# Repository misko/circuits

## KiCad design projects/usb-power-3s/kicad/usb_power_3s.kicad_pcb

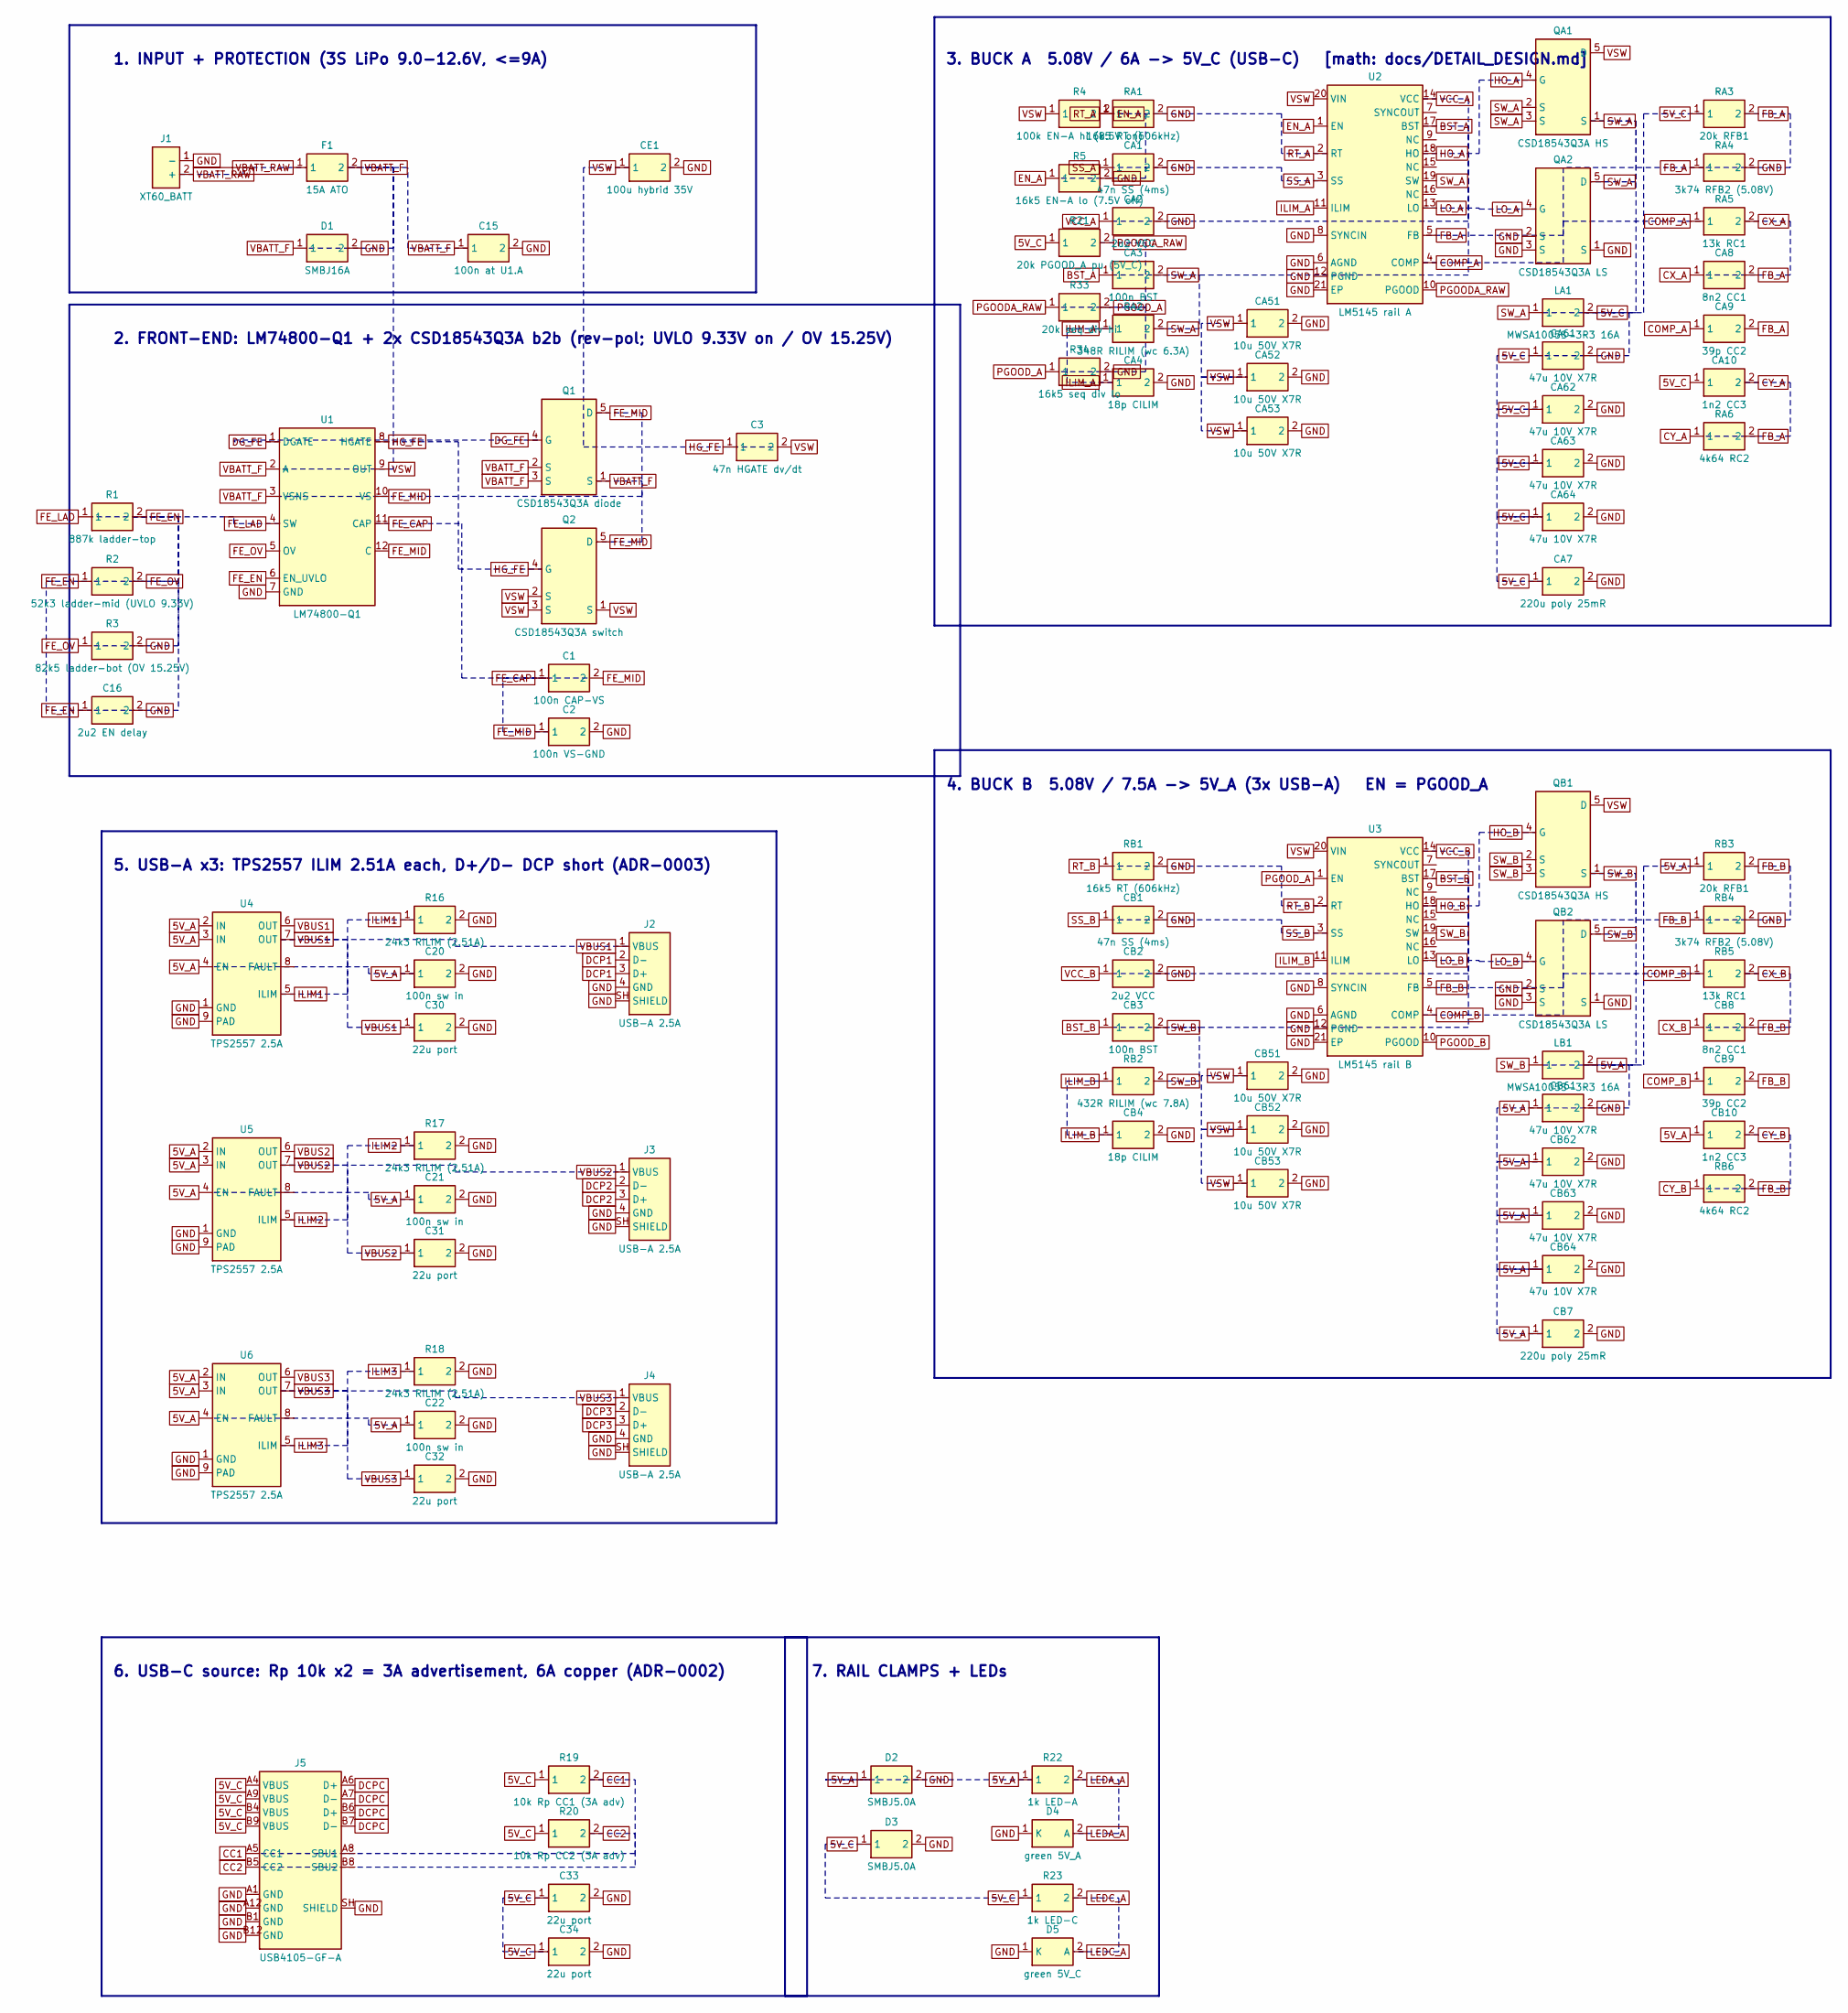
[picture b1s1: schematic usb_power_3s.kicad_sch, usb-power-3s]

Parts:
C1: 100n CAP-VS; C_0402_1005Metric
C2: 100n VS-GND; C_0402_1005Metric
C3: 47n HGATE dv/dt; C_0402_1005Metric
C15: 100n at U1.A; C_0402_1005Metric
C16: 2u2 EN delay; C_0603_1608Metric
C20, C21, C22: 100n sw in; C_0402_1005Metric
C30, C31, C32, C33, C34: 22u port; C_1206_3216Metric
CA1: 47n SS (4ms); C_0402_1005Metric
CA2: 2u2 VCC; C_0603_1608Metric
CA3: 100n BST; C_0402_1005Metric
CA4: 18p CILIM; C_0402_1005Metric
CA7: 220u poly 25mR; CP_Elec_6.3x5.9
CA8: 8n2 CC1; C_0402_1005Metric
CA9: 39p CC2; C_0402_1005Metric
CA10: 1n2 CC3; C_0402_1005Metric
CA51, CA52, CA53: 10u 50V X7R; C_1210_3225Metric
CA61, CA62, CA63, CA64: 47u 10V X7R; C_1210_3225Metric
CB1: 47n SS (4ms); C_0402_1005Metric
CB2: 2u2 VCC; C_0603_1608Metric
CB3: 100n BST; C_0402_1005Metric
CB4: 18p CILIM; C_0402_1005Metric
CB7: 220u poly 25mR; CP_Elec_6.3x5.9
CB8: 8n2 CC1; C_0402_1005Metric
CB9: 39p CC2; C_0402_1005Metric
CB10: 1n2 CC3; C_0402_1005Metric
CB51, CB52, CB53: 10u 50V X7R; C_1210_3225Metric
CB61, CB62, CB63, CB64: 47u 10V X7R; C_1210_3225Metric
CE1: 100u hybrid 35V; CP_Elec_8x10
D1: SMBJ16A; D_SMB
D2, D3: SMBJ5.0A; D_SMB
D4: green 5V_A; LED_0805_2012Metric
D5: green 5V_C; LED_0805_2012Metric
F1: 15A ATO; FuseHolder_ATO_FLR_EdgeTrim
J1: XT60_BATT; XT60PW-M_EdgeTrim
J2, J3, J4: USB-A 2.5A; USB_A_CNCTech_1001-011-01101_Horizontal
J5: USB4105-GF-A; USB_C_Receptacle_GCT_USB4105-xx-A_16P_TopMnt_Horizontal
LA1: MWSA1005S-3R3 16A; L_Sunlord_MWSA1005S
LB1: MWSA1005S-3R3 16A; L_Sunlord_MWSA1005S
Q1: CSD18543Q3A diode; VSON-8_3.3x3.3mm_P0.65mm_NexFET
Q2: CSD18543Q3A switch; VSON-8_3.3x3.3mm_P0.65mm_NexFET
QA1: CSD18543Q3A HS; VSON-8_3.3x3.3mm_P0.65mm_NexFET
QA2: CSD18543Q3A LS; VSON-8_3.3x3.3mm_P0.65mm_NexFET
QB1: CSD18543Q3A HS; VSON-8_3.3x3.3mm_P0.65mm_NexFET
QB2: CSD18543Q3A LS; VSON-8_3.3x3.3mm_P0.65mm_NexFET
R1: 887k ladder-top; R_0402_1005Metric
R2: 52k3 ladder-mid (UVLO 9.33V); R_0402_1005Metric
R3: 82k5 ladder-bot (OV 15.25V); R_0402_1005Metric
R4: 100k EN-A hi (8.5V on); R_0402_1005Metric
R5: 16k5 EN-A lo (7.5V off); R_0402_1005Metric
R16, R17, R18: 24k3 RILIM (2.51A); R_0402_1005Metric
R19: 10k Rp CC1 (3A adv); R_0402_1005Metric
R20: 10k Rp CC2 (3A adv); R_0402_1005Metric
R21: 20k PGOOD_A pu (5V_C); R_0402_1005Metric
R22: 1k LED-A; R_0402_1005Metric
R23: 1k LED-C; R_0402_1005Metric
R33: 20k seq div hi; R_0402_1005Metric
R34: 16k5 seq div lo; R_0402_1005Metric
RA1: 16k5 RT (606kHz); R_0402_1005Metric
RA2: 348R RILIM (wc 6.3A); R_0402_1005Metric
RA3: 20k RFB1; R_0402_1005Metric
RA4: 3k74 RFB2 (5.08V); R_0402_1005Metric
RA5: 13k RC1; R_0402_1005Metric
RA6: 4k64 RC2; R_0402_1005Metric
RB1: 16k5 RT (606kHz); R_0402_1005Metric
RB2: 432R RILIM (wc 7.8A); R_0402_1005Metric
RB3: 20k RFB1; R_0402_1005Metric
RB4: 3k74 RFB2 (5.08V); R_0402_1005Metric
RB5: 13k RC1; R_0402_1005Metric
RB6: 4k64 RC2; R_0402_1005Metric
U1: LM74800-Q1; WSON-12_3x3_P0.5_LM74800DRR
U2: LM5145 rail A; VQFN-20_3.5x4.5_P0.5_LM5145RGY
U3: LM5145 rail B; VQFN-20_3.5x4.5_P0.5_LM5145RGY
U4, U5, U6: TPS2557 2.5A; VSON-8-1EP_3x3mm_P0.65mm_EP1.65x2.4mm

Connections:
5V_A: C20.1, C21.1, C22.1, CB7.1, CB10.1, CB61.1, CB62.1, CB63.1, CB64.1, D2.1, LB1.2, R22.1, RB3.1, U4.2 (IN), U4.3 (IN), U4.4 (EN), U5.2 (IN), U5.3 (IN), U5.4 (EN), U6.2 (IN), U6.3 (IN), U6.4 (EN)
5V_C: C33.1, C34.1, CA7.1, CA10.1, CA61.1, CA62.1, CA63.1, CA64.1, D3.1, J5.A4 (VBUS), J5.A9 (VBUS), J5.B4 (VBUS), J5.B9 (VBUS), LA1.2, R19.1, R20.1, R21.1, R23.1, RA3.1
BST_A: CA3.1, U2.17 (BST)
BST_B: CB3.1, U3.17 (BST)
CC1: J5.A5 (CC1), R19.2
CC2: J5.B5 (CC2), R20.2
COMP_A: CA9.1, RA5.1, U2.4 (COMP)
COMP_B: CB9.1, RB5.1, U3.4 (COMP)
CX_A: CA8.1, RA5.2
CX_B: CB8.1, RB5.2
CY_A: CA10.2, RA6.1
CY_B: CB10.2, RB6.1
DCP1: J2.2 (D-), J2.3 (D+)
DCP2: J3.2 (D-), J3.3 (D+)
DCP3: J4.2 (D-), J4.3 (D+)
DCPC: J5.A6 (D+), J5.A7 (D-), J5.B6 (D+), J5.B7 (D-)
DG_FE: Q1.4 (G), U1.1 (DGATE)
EN_A: R4.2, R5.1, U2.1 (EN)
FB_A: CA8.2, CA9.2, RA3.2, RA4.1, RA6.2, U2.5 (FB)
FB_B: CB8.2, CB9.2, RB3.2, RB4.1, RB6.2, U3.5 (FB)
FE_CAP: C1.1, U1.11 (CAP)
FE_EN: C16.1, R1.2, R2.1, U1.6 (EN_UVLO)
FE_LAD: R1.1, U1.4 (SW)
FE_MID: C1.2, C2.1, Q1.5 (D), Q2.5 (D), U1.10 (VS), U1.12 (C)
FE_OV: R2.2, R3.1, U1.5 (OV)
GND: C2.2, C15.2, C16.2, C20.2, C21.2, C22.2, C30.2, C31.2, C32.2, C33.2, C34.2, CA1.2, CA2.2, CA4.2, CA7.2, CA51.2, CA52.2, CA53.2, CA61.2, CA62.2, CA63.2, CA64.2, CB1.2, CB2.2, CB4.2, CB7.2, CB51.2, CB52.2, CB53.2, CB61.2, CB62.2, CB63.2, CB64.2, CE1.2, D1.2, D2.2, D3.2, D4.1 (K), D5.1 (K), J1.1 (-), J2.4 (GND), J2.SH (SHIELD), J3.4 (GND), J3.SH (SHIELD), J4.4 (GND), J4.SH (SHIELD), J5.A1 (GND), J5.A12 (GND), J5.B1 (GND), J5.B12 (GND), J5.SH (SHIELD), QA2.1 (S), QA2.2 (S), QA2.3 (S), QB2.1 (S), QB2.2 (S), QB2.3 (S), R3.2, R5.2, R16.2, R17.2, R18.2, R34.2, RA1.2, RA4.2, RB1.2, RB4.2, U1.7 (GND), U2.6 (AGND), U2.8 (SYNCIN), U2.12 (PGND), U2.21 (EP), U3.6 (AGND), U3.8 (SYNCIN), U3.12 (PGND), U3.21 (EP), U4.1 (GND), U4.9 (PAD), U5.1 (GND), U5.9 (PAD), U6.1 (GND), U6.9 (PAD)
HG_FE: C3.1, Q2.4 (G), U1.8 (HGATE)
HO_A: QA1.4 (G), U2.18 (HO)
HO_B: QB1.4 (G), U3.18 (HO)
ILIM1: R16.1, U4.5 (ILIM)
ILIM2: R17.1, U5.5 (ILIM)
ILIM3: R18.1, U6.5 (ILIM)
ILIM_A: CA4.1, RA2.1, U2.11 (ILIM)
ILIM_B: CB4.1, RB2.1, U3.11 (ILIM)
LEDA_A: D4.2 (A), R22.2
LEDC_A: D5.2 (A), R23.2
LO_A: QA2.4 (G), U2.13 (LO)
LO_B: QB2.4 (G), U3.13 (LO)
PGOODA_RAW: R21.2, R33.1, U2.10 (PGOOD)
PGOOD_A: R33.2, R34.1, U3.1 (EN)
PGOOD_B: U3.10 (PGOOD)
RT_A: RA1.1, U2.2 (RT)
RT_B: RB1.1, U3.2 (RT)
SS_A: CA1.1, U2.3 (SS)
SS_B: CB1.1, U3.3 (SS)
SW_A: CA3.2, LA1.1, QA1.1 (S), QA1.2 (S), QA1.3 (S), QA2.5 (D), RA2.2, U2.19 (SW)
SW_B: CB3.2, LB1.1, QB1.1 (S), QB1.2 (S), QB1.3 (S), QB2.5 (D), RB2.2, U3.19 (SW)
VBATT_F: C15.1, D1.1, F1.2, Q1.1 (S), Q1.2 (S), Q1.3 (S), U1.2 (A), U1.3 (VSNS)
VBATT_RAW: F1.1, J1.2 (+)
VBUS1: C30.1, J2.1 (VBUS), U4.6 (OUT), U4.7 (OUT)
VBUS2: C31.1, J3.1 (VBUS), U5.6 (OUT), U5.7 (OUT)
VBUS3: C32.1, J4.1 (VBUS), U6.6 (OUT), U6.7 (OUT)
VCC_A: CA2.1, U2.14 (VCC)
VCC_B: CB2.1, U3.14 (VCC)
VSW: C3.2, CA51.1, CA52.1, CA53.1, CB51.1, CB52.1, CB53.1, CE1.1, Q2.1 (S), Q2.2 (S), Q2.3 (S), QA1.5 (D), QB1.5 (D), R4.1, U1.9 (OUT), U2.20 (VIN), U3.20 (VIN)

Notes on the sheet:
1. INPUT + PROTECTION (3S LiPo 9.0-12.6V, <=9A)
2. FRONT-END: LM74800-Q1 + 2x CSD18543Q3A b2b (rev-pol; UVLO 9.33V on / OV 15.25V)
3. BUCK A 5.08V / 6A -> 5V_C (USB-C) [math: docs/DETAIL_DESIGN.md]
4. BUCK B 5.08V / 7.5A -> 5V_A (3x USB-A) EN = PGOOD_A
5. USB-A x3: TPS2557 ILIM 2.51A each, D+/D- DCP short (ADR-0003)
6. USB-C source: Rp 10k x2 = 3A advertisement, 6A copper (ADR-0002)
7. RAIL CLAMPS + LEDs

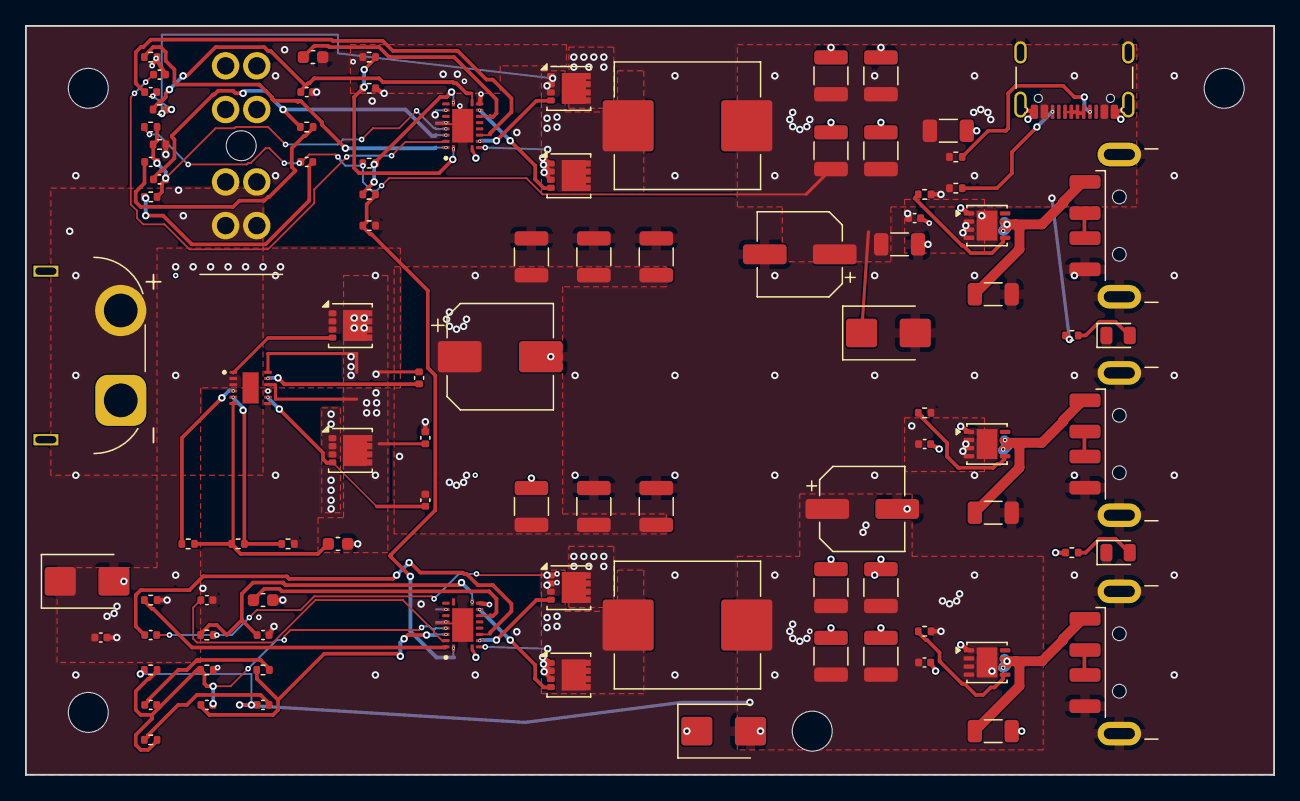
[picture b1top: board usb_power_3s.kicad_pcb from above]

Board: 4 copper layers, 100.0 x 60.0 mm, 100 parts (0 on the bottom side), 54 nets.

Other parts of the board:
H1, H2, H3, H4: MountingHole_3.2mm_M3

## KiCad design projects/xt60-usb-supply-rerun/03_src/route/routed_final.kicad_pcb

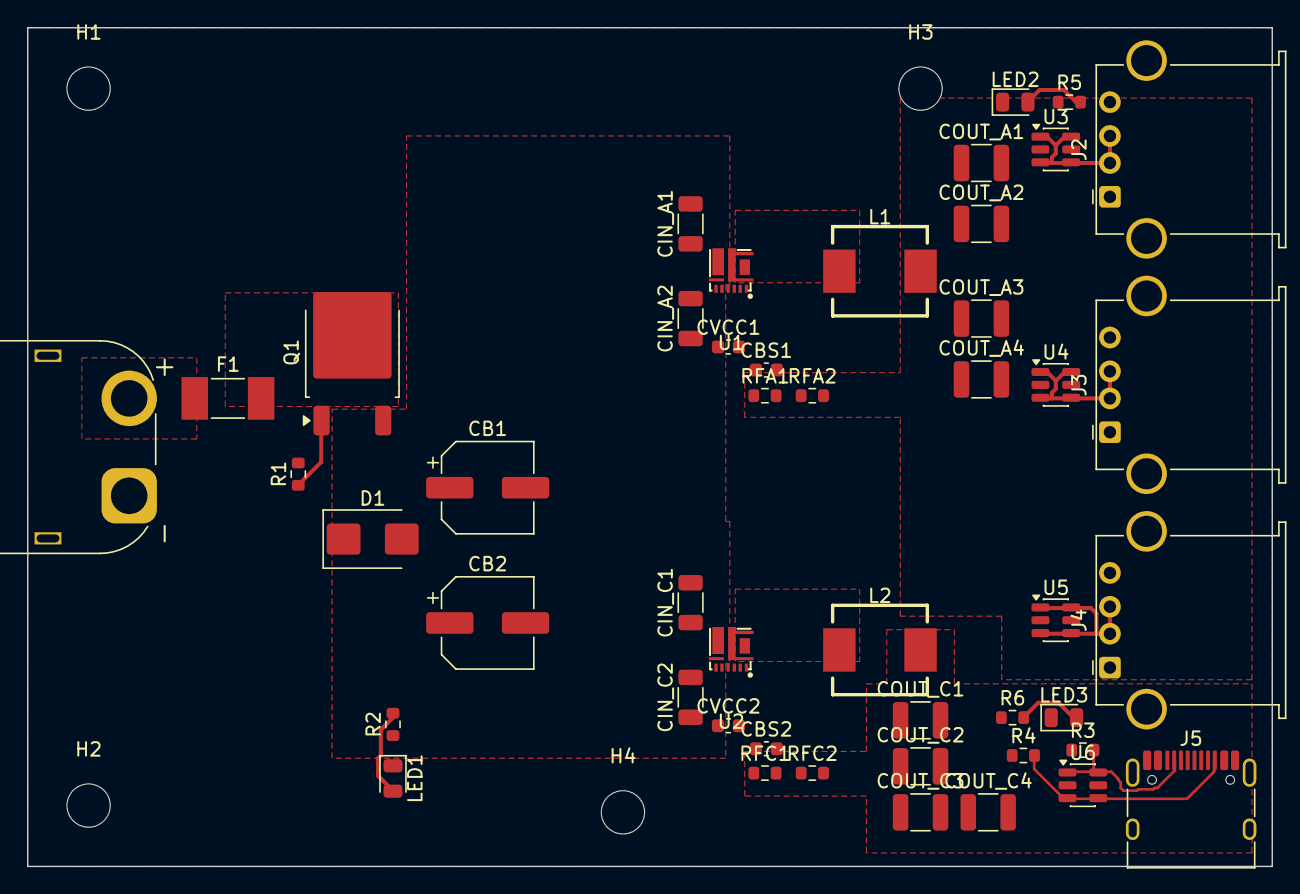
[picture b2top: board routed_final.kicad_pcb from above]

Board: 4 copper layers, 92.0 x 62.0 mm, 51 parts (0 on the bottom side), 23 nets.

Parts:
CB1, CB2: 100uF 25V polymer; CP_Elec_6.3x5.9
CBS1, CBS2: 100nF; C_0603_1608Metric
CIN_A1, CIN_A2: 10uF 25V X7R; C_1206_3216Metric
CIN_C1, CIN_C2: 10uF 25V X7R; C_1206_3216Metric
COUT_A1, COUT_A2, COUT_A3, COUT_A4: 22uF 16V X7R; C_1210_3225Metric
COUT_C1, COUT_C2, COUT_C3, COUT_C4: 22uF 16V X7R; C_1210_3225Metric
CVCC1, CVCC2: 2.2uF; C_0603_1608Metric
D1: SMBJ15A; D_SMB
F1: 15A; Fuse_Littelfuse-NANO2-451_453
H1, H2, H3, H4: MountingHole_3.2mm_M3
J1: XT60PW-M; AMASS_XT60PW-M_1x02_P7.20mm_Horizontal
J2, J3, J4: USB-A; USB_A_Stewart_SS-52100-001_Horizontal
J5: TYPE-C-31-M-12A; USB_C_Receptacle_HRO_TYPE-C-31-M-12
L1: 1.5uH; L_FXL0630_7.0x6.6mm
L2: 2.2uH; L_FXL0630_7.0x6.6mm
LED1: red; LED_0805_2012Metric
LED2, LED3: green; LED_0805_2012Metric
Q1: AOD4185; TO-252-2
R1: 100k; R_0603_1608Metric
R2, R5, R6: 1k; R_0603_1608Metric
R3, R4: 10k 1%; R_0603_1608Metric
RFA1: 22k 1%; R_0603_1608Metric
RFA2: 3k 1%; R_0603_1608Metric
RFC1: 22k 1%; R_0603_1608Metric
RFC2: 3k 1%; R_0603_1608Metric
U1, U2: SY8368QNC; QFN3x3-10_FC_SY8368
U3, U4, U5, U6: USBLC6-2SC6; SOT-23-6

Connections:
5V_A: COUT_A1.1, COUT_A2.1, COUT_A3.1, COUT_A4.1, J2.1, J3.1, J4.1, L1.2, R5.1, RFA1.1, U3.5, U4.5, U5.5
5V_C: COUT_C1.1, COUT_C2.1, COUT_C3.1, COUT_C4.1, J5.A4, J5.A9, J5.B4, J5.B9, L2.2, R3.1, R4.1, R6.1, RFC1.1, U6.5
BST_A: CBS1.1, U1.6
BST_C: CBS2.1, U2.6
CC1: J5.A5, R3.2, U6.1, U6.6
CC2: J5.B5, R4.2, U6.3, U6.4
DCP1: J2.2, J2.3, U3.1, U3.3, U3.4, U3.6
DCP2: J3.2, J3.3, U4.1, U4.3, U4.4, U4.6
DCP3: J4.2, J4.3, U5.1, U5.3, U5.4, U5.6
FB_A: RFA1.2, RFA2.1, U1.4
FB_C: RFC1.2, RFC2.1, U2.4
GND: CB1.2, CB2.2, CIN_A1.2, CIN_A2.2, CIN_C1.2, CIN_C2.2, COUT_A1.2, COUT_A2.2, COUT_A3.2, COUT_A4.2, COUT_C1.2, COUT_C2.2, COUT_C3.2, COUT_C4.2, CVCC1.2, CVCC2.2, D1.2, J1.1, J2.4, J2.SH, J3.4, J3.SH, J4.4, J4.SH, J5.A1, J5.A12, J5.B1, J5.B12, J5.SH, LED1.1, LED2.1, LED3.1, R1.2, RFA2.2, RFC2.2, U1.3, U1.9, U2.3, U2.9, U3.2, U4.2, U5.2, U6.2
LED1_A: LED1.2, R2.2
LED2_A: LED2.2, R5.2
LED3_A: LED3.2, R6.2
PFET_G: Q1.1, R1.1
SW_A: CBS1.2, L1.1, U1.10
SW_C: CBS2.2, L2.1, U2.10
VBAT_F: F1.2, Q1.2
VBAT_P: CB1.1, CB2.1, CIN_A1.1, CIN_A2.1, CIN_C1.1, CIN_C2.1, D1.1, Q1.3, R2.1, U1.1, U1.7, U1.8, U2.1, U2.7, U2.8
VBAT_RAW: F1.1, J1.2
VCC_A: CVCC1.1, U1.5
VCC_C: CVCC2.1, U2.5

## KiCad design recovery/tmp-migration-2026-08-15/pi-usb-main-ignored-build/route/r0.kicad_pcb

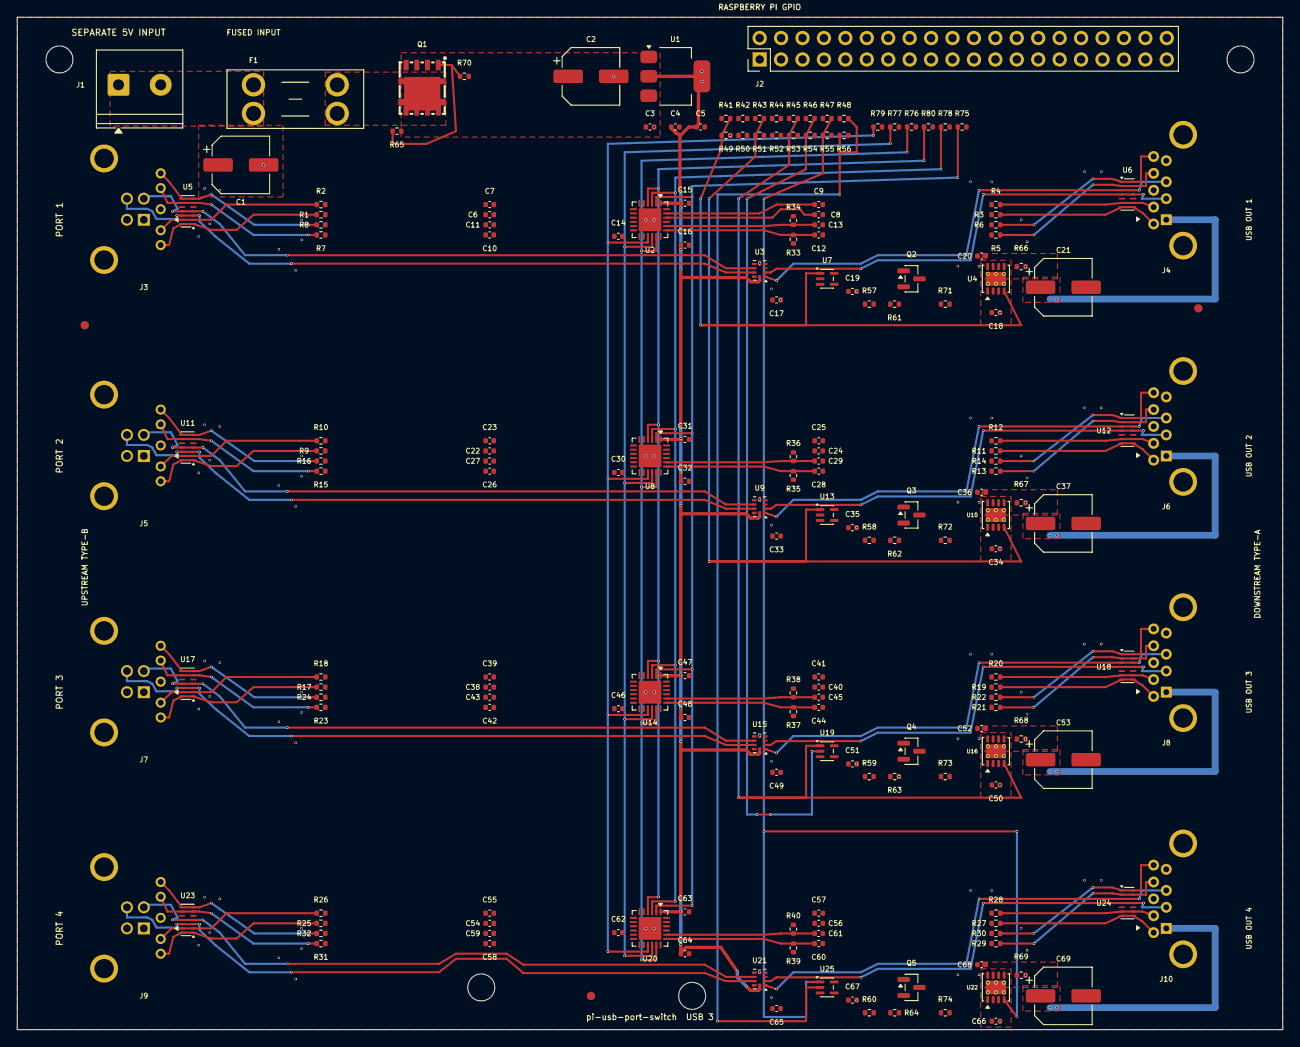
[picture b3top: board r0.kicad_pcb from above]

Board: 4 copper layers, 150.0 x 120.0 mm, 197 parts (0 on the bottom side), 164 nets.

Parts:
C1, C2: 180uF; CP_Elec_6.3x5.8
C3, C6, C7, C8, C9, C10, C11, C14, C15, C17, C18, C19, C20, C22, C23, C24, C25, C26, C27, C30, C31, C33, C34, C35, C36, C38, C39, C40, C41, C42, C43, C46, C47, C49, C50, C51, C52, C54, C55, C56, C57, C58, C59, C62, C63, C65, C66, C67, C68: 100nF; C_0402_1005Metric
C4: 1uF; C_0402_1005Metric
C5, C16, C32, C48, C64: 10uF; C_0402_1005Metric
C12, C13, C28, C29, C44, C45, C60, C61: 330nF; C_0402_1005Metric
C21, C37, C53, C69: 150uF; CP_Elec_6.3x5.8
F1: C5249699; Keystone_3568_Mini_Blade_Fuse_Holder
FID1, FID2, FID3: Fiducial_1mm_Mask2mm
H1, H2, H3, H4: MountingHole_3.2mm_M3
J1: C3819953; Phoenix_1935161_PT_1p5_2_5p0_H
J2: C5364405; PinHeader_2x20_P2.54mm_Vertical
J3, J5, J7, J9: C5334230; Wurth_692221030100_USB3_B
J4, J6, J8, J10: 692121030100; Wurth_692121030100_USB3_A
Q1: C397981; PowerDI5060-8
Q2, Q3, Q4, Q5: C85049; SOT-23
R1, R2, R3, R4, R5, R6, R7, R8, R9, R10, R11, R12, R13, R14, R15, R16, R17, R18, R19, R20, R21, R22, R23, R24, R25, R26, R27, R28, R29, R30, R31, R32: 2.2Ω; R_0402_1005Metric
R33, R34, R35, R36, R37, R38, R39, R40: 220kΩ; R_0402_1005Metric
R41, R42, R43, R44, R45, R46, R47, R48: 1kΩ; R_0402_1005Metric
R49, R50, R51, R52, R53, R54, R55, R56, R57, R58, R59, R60, R61, R62, R63, R64, R65, R66, R67, R68, R69: 100kΩ; R_0402_1005Metric
R70: 1MΩ; R_0402_1005Metric
R71, R72, R73, R74: 10kΩ; R_0402_1005Metric
R75, R76, R77, R78, R79, R80: 4.7kΩ; R_0402_1005Metric
U1: C7527500; SOT-223-3_TabPin2
U2, U8, U14, U20: C2675181; TUSB522P_RGE24_4x4_P0.5
U3, U9, U15, U21: C129313; TS3USB221E_RSE10_2x1.5_P0.4
U4, U10, U16, U22: C130056; VSON-8-1EP_3x3mm_P0.65mm_EP1.65x2.4mm_ThermalVias
U5, U6, U11, U12, U17, U18, U23, U24: C962978; TPD6E05U06_RVZ14_3.5x1.35_P0.5
U7, U13, U19, U25: C7832; SC-70-5

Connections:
3V3: C4.1, C5.1, C14.1, C15.1, C16.1, C17.1, C19.1, C30.1, C31.1, C32.1, C33.1, C35.1, C46.1, C47.1, C48.1, C49.1, C51.1, C62.1, C63.1, C64.1, C65.1, C67.1, R57.1, R58.1, R59.1, R60.1, R71.1, R72.1, R73.1, R74.1, U1.2, U2.1, U2.13, U3.10, U7.5, U8.1, U8.13, U9.10, U13.5, U14.1, U14.13, U15.10, U19.5, U20.1, U20.13, U21.10, U25.5
DATA_EN1: R42.2, R50.1, U7.2
DATA_EN2: R44.2, R52.1, U13.2
DATA_EN3: R46.2, R54.1, U19.2
DATA_EN4: R48.2, R56.1, U25.2
DATA_OK1: Q2.1, U2.5, U7.4
DATA_OK2: Q3.1, U8.5, U13.4
DATA_OK3: Q4.1, U14.5, U19.4
DATA_OK4: Q5.1, U20.5, U25.4
EXT_5V_FUSED: F1.2, Q1.5, Q1.6, Q1.7, Q1.8
EXT_5V_RAW: C1.1, F1.1, J1.1
GND: C1.2, C2.2, C3.2, C4.2, C5.2, C14.2, C15.2, C16.2, C17.2, C18.2, C19.2, C20.2, C21.2, C30.2, C31.2, C32.2, C33.2, C34.2, C35.2, C36.2, C37.2, C46.2, C47.2, C48.2, C49.2, C50.2, C51.2, C52.2, C53.2, C62.2, C63.2, C64.2, C65.2, C66.2, C67.2, C68.2, C69.2, J1.2, J2.6, J2.9, J2.14, J2.20, J2.25, J2.30, J2.34, J2.39, J3.4, J3.7, J3.10, J4.4, J4.7, J4.10, J5.4, J5.7, J5.10, J6.4, J6.7, J6.10, J7.4, J7.7, J7.10, J8.4, J8.7, J8.10, J9.4, J9.7, J9.10, J10.4, J10.7, J10.10, Q2.2, Q3.2, Q4.2, Q5.2, R33.2, R34.2, R35.2, R36.2, R37.2, R38.2, R39.2, R40.2, R49.2, R50.2, R51.2, R52.2, R53.2, R54.2, R55.2, R56.2, R61.2, R62.2, R63.2, R64.2, R65.2, R66.2, R67.2, R68.2, R69.2, R75.2, R76.2, R77.2, R78.2, R79.2, R80.2, U1.1, U2.10, U2.21, U2.25, U3.5, U4.1, U4.9, U5.5, U5.10, U6.5, U6.10, U7.3, U8.10, U8.21, U8.25, U9.5, U10.1, U10.9, U11.5, U11.10, U12.5, U12.10, U13.3, U14.10, U14.21, U14.25, U15.5, U16.1, U16.9, U17.5, U17.10, U18.5, U18.10, U19.3, U20.10, U20.21, U20.25, U21.5, U22.1, U22.9, U23.5, U23.10, U24.5, U24.10, U25.3
GPIO5_RAW: J2.29, R47.1
GPIO6_RAW: J2.31, R48.1
GPIO17_RAW: J2.11, R41.1
GPIO22_RAW: J2.15, R43.1
GPIO23_RAW: J2.16, R44.1
GPIO24_RAW: J2.18, R45.1
GPIO25_RAW: J2.22, R46.1
GPIO27_RAW: J2.13, R42.1
ILIM1: R66.1, U4.5
ILIM2: R67.1, U10.5
ILIM3: R68.1, U16.5
ILIM4: R69.1, U22.5
P5V_PROTECTED: C2.1, C3.1, C18.1, C34.1, C50.1, C66.1, Q1.2, Q1.3, Q1.4, R70.1, U1.3, U4.2, U4.3, U10.2, U10.3, U16.2, U16.3, U22.2, U22.3
PWR_EN1: R41.2, R49.1, U4.4, U7.1
PWR_EN2: R43.2, R51.1, U10.4, U13.1
PWR_EN3: R45.2, R53.1, U16.4, U19.1
PWR_EN4: R47.2, R55.1, U22.4, U25.1
RPP_GATE: Q1.1, R65.1, R70.2
TUSB_DE1: R77.1, U2.16, U8.16, U14.16, U20.16
TUSB_DE2: R78.1, U2.3, U8.3, U14.3, U20.3
TUSB_EQ1: R75.1, U2.2, U8.2, U14.2, U20.2
TUSB_EQ2: R76.1, U2.17, U8.17, U14.17, U20.17
TUSB_OS1: R79.1, U2.15, U8.15, U14.15, U20.15
TUSB_OS2: R80.1, U2.4, U8.4, U14.4, U20.4
USB1_HS_DN_N: J4.2, U3.2, U6.4, U6.11
USB1_HS_DN_P: J4.3, U3.1, U6.3, U6.12
USB1_HS_UP_N: J3.2, U3.7, U5.4, U5.11
USB1_HS_UP_P: J3.3, U3.8, U5.3, U5.12
USB1_SS_RX_DN_CONN_N: J4.5, R6.1, U6.1, U6.14
USB1_SS_RX_DN_CONN_P: J4.6, R5.1, U6.2, U6.13
USB1_SS_RX_DN_IC_N: C13.2, R34.1, U2.20
USB1_SS_RX_DN_IC_P: C12.2, R33.1, U2.19
USB1_SS_RX_DN_MID_N: C13.1, R6.2
USB1_SS_RX_DN_MID_P: C12.1, R5.2
USB1_SS_RX_UP_CONN_N: J3.5, R8.1, U5.7, U5.8
USB1_SS_RX_UP_CONN_P: J3.6, R7.1, U5.6, U5.9
USB1_SS_RX_UP_IC_N: C11.1, U2.11
USB1_SS_RX_UP_IC_P: C10.1, U2.12
USB1_SS_RX_UP_MID_N: C11.2, R8.2
USB1_SS_RX_UP_MID_P: C10.2, R7.2
USB1_SS_TX_DN_CONN_N: J4.8, R4.1, U6.6, U6.9
USB1_SS_TX_DN_CONN_P: J4.9, R3.1, U6.7, U6.8
USB1_SS_TX_DN_IC_N: C9.1, U2.23
USB1_SS_TX_DN_IC_P: C8.1, U2.22
USB1_SS_TX_DN_MID_N: C9.2, R4.2
USB1_SS_TX_DN_MID_P: C8.2, R3.2
USB1_SS_TX_UP_CONN_N: J3.8, R2.1, U5.2, U5.13
USB1_SS_TX_UP_CONN_P: J3.9, R1.1, U5.1, U5.14
USB1_SS_TX_UP_IC_N: C7.2, U2.8
USB1_SS_TX_UP_IC_P: C6.2, U2.9
USB1_SS_TX_UP_MID_N: C7.1, R2.2
USB1_SS_TX_UP_MID_P: C6.1, R1.2
USB2_HS_DN_N: J6.2, U9.2, U12.4, U12.11
USB2_HS_DN_P: J6.3, U9.1, U12.3, U12.12
USB2_HS_UP_N: J5.2, U9.7, U11.4, U11.11
USB2_HS_UP_P: J5.3, U9.8, U11.3, U11.12
USB2_OE1: Q2.3, R57.2, U3.6
USB2_OE2: Q3.3, R58.2, U9.6
USB2_OE3: Q4.3, R59.2, U15.6
USB2_OE4: Q5.3, R60.2, U21.6
USB2_SEL1: R61.1, U3.9
USB2_SEL2: R62.1, U9.9
USB2_SEL3: R63.1, U15.9
USB2_SEL4: R64.1, U21.9
USB2_SS_RX_DN_CONN_N: J6.5, R14.1, U12.1, U12.14
USB2_SS_RX_DN_CONN_P: J6.6, R13.1, U12.2, U12.13
USB2_SS_RX_DN_IC_N: C29.2, R36.1, U8.20
USB2_SS_RX_DN_IC_P: C28.2, R35.1, U8.19
USB2_SS_RX_DN_MID_N: C29.1, R14.2
USB2_SS_RX_DN_MID_P: C28.1, R13.2
USB2_SS_RX_UP_CONN_N: J5.5, R16.1, U11.7, U11.8
USB2_SS_RX_UP_CONN_P: J5.6, R15.1, U11.6, U11.9
USB2_SS_RX_UP_IC_N: C27.1, U8.11
USB2_SS_RX_UP_IC_P: C26.1, U8.12
USB2_SS_RX_UP_MID_N: C27.2, R16.2
USB2_SS_RX_UP_MID_P: C26.2, R15.2
USB2_SS_TX_DN_CONN_N: J6.8, R12.1, U12.6, U12.9
USB2_SS_TX_DN_CONN_P: J6.9, R11.1, U12.7, U12.8
USB2_SS_TX_DN_IC_N: C25.1, U8.23
USB2_SS_TX_DN_IC_P: C24.1, U8.22
USB2_SS_TX_DN_MID_N: C25.2, R12.2
USB2_SS_TX_DN_MID_P: C24.2, R11.2
USB2_SS_TX_UP_CONN_N: J5.8, R10.1, U11.2, U11.13
USB2_SS_TX_UP_CONN_P: J5.9, R9.1, U11.1, U11.14
USB2_SS_TX_UP_IC_N: C23.2, U8.8
USB2_SS_TX_UP_IC_P: C22.2, U8.9
USB2_SS_TX_UP_MID_N: C23.1, R10.2
USB2_SS_TX_UP_MID_P: C22.1, R9.2
USB3_HS_DN_N: J8.2, U15.2, U18.4, U18.11
USB3_HS_DN_P: J8.3, U15.1, U18.3, U18.12
USB3_HS_UP_N: J7.2, U15.7, U17.4, U17.11
USB3_HS_UP_P: J7.3, U15.8, U17.3, U17.12
USB3_SS_RX_DN_CONN_N: J8.5, R22.1, U18.1, U18.14
USB3_SS_RX_DN_CONN_P: J8.6, R21.1, U18.2, U18.13
USB3_SS_RX_DN_IC_N: C45.2, R38.1, U14.20
USB3_SS_RX_DN_IC_P: C44.2, R37.1, U14.19
USB3_SS_RX_DN_MID_N: C45.1, R22.2
USB3_SS_RX_DN_MID_P: C44.1, R21.2
USB3_SS_RX_UP_CONN_N: J7.5, R24.1, U17.7, U17.8
USB3_SS_RX_UP_CONN_P: J7.6, R23.1, U17.6, U17.9
USB3_SS_RX_UP_IC_N: C43.1, U14.11
USB3_SS_RX_UP_IC_P: C42.1, U14.12
USB3_SS_RX_UP_MID_N: C43.2, R24.2
USB3_SS_RX_UP_MID_P: C42.2, R23.2
USB3_SS_TX_DN_CONN_N: J8.8, R20.1, U18.6, U18.9
USB3_SS_TX_DN_CONN_P: J8.9, R19.1, U18.7, U18.8
USB3_SS_TX_DN_IC_N: C41.1, U14.23
USB3_SS_TX_DN_IC_P: C40.1, U14.22
USB3_SS_TX_DN_MID_N: C41.2, R20.2
USB3_SS_TX_DN_MID_P: C40.2, R19.2
USB3_SS_TX_UP_CONN_N: J7.8, R18.1, U17.2, U17.13
USB3_SS_TX_UP_CONN_P: J7.9, R17.1, U17.1, U17.14
USB3_SS_TX_UP_IC_N: C39.2, U14.8
USB3_SS_TX_UP_IC_P: C38.2, U14.9
USB3_SS_TX_UP_MID_N: C39.1, R18.2
USB3_SS_TX_UP_MID_P: C38.1, R17.2
USB4_HS_DN_N: J10.2, U21.2, U24.4, U24.11
USB4_HS_DN_P: J10.3, U21.1, U24.3, U24.12
USB4_HS_UP_N: J9.2, U21.7, U23.4, U23.11
USB4_HS_UP_P: J9.3, U21.8, U23.3, U23.12
USB4_SS_RX_DN_CONN_N: J10.5, R30.1, U24.1, U24.14
USB4_SS_RX_DN_CONN_P: J10.6, R29.1, U24.2, U24.13
USB4_SS_RX_DN_IC_N: C61.2, R40.1, U20.20
USB4_SS_RX_DN_IC_P: C60.2, R39.1, U20.19
USB4_SS_RX_DN_MID_N: C61.1, R30.2
USB4_SS_RX_DN_MID_P: C60.1, R29.2
USB4_SS_RX_UP_CONN_N: J9.5, R32.1, U23.7, U23.8
USB4_SS_RX_UP_CONN_P: J9.6, R31.1, U23.6, U23.9
USB4_SS_RX_UP_IC_N: C59.1, U20.11
USB4_SS_RX_UP_IC_P: C58.1, U20.12
USB4_SS_RX_UP_MID_N: C59.2, R32.2
USB4_SS_RX_UP_MID_P: C58.2, R31.2
USB4_SS_TX_DN_CONN_N: J10.8, R28.1, U24.6, U24.9
USB4_SS_TX_DN_CONN_P: J10.9, R27.1, U24.7, U24.8
USB4_SS_TX_DN_IC_N: C57.1, U20.23
USB4_SS_TX_DN_IC_P: C56.1, U20.22
USB4_SS_TX_DN_MID_N: C57.2, R28.2
USB4_SS_TX_DN_MID_P: C56.2, R27.2
USB4_SS_TX_UP_CONN_N: J9.8, R26.1, U23.2, U23.13
USB4_SS_TX_UP_CONN_P: J9.9, R25.1, U23.1, U23.14
USB4_SS_TX_UP_IC_N: C55.2, U20.8
USB4_SS_TX_UP_IC_P: C54.2, U20.9
USB4_SS_TX_UP_MID_N: C55.1, R26.2
USB4_SS_TX_UP_MID_P: C54.1, R25.2
VBUS1_SW: C20.1, C21.1, J4.1, U4.6, U4.7
VBUS2_SW: C36.1, C37.1, J6.1, U10.6, U10.7
VBUS3_SW: C52.1, C53.1, J8.1, U16.6, U16.7
VBUS4_SW: C68.1, C69.1, J10.1, U22.6, U22.7
VBUS_FAULT1_N: R71.2, U4.8
VBUS_FAULT2_N: R72.2, U10.8
VBUS_FAULT3_N: R73.2, U16.8
VBUS_FAULT4_N: R74.2, U22.8
